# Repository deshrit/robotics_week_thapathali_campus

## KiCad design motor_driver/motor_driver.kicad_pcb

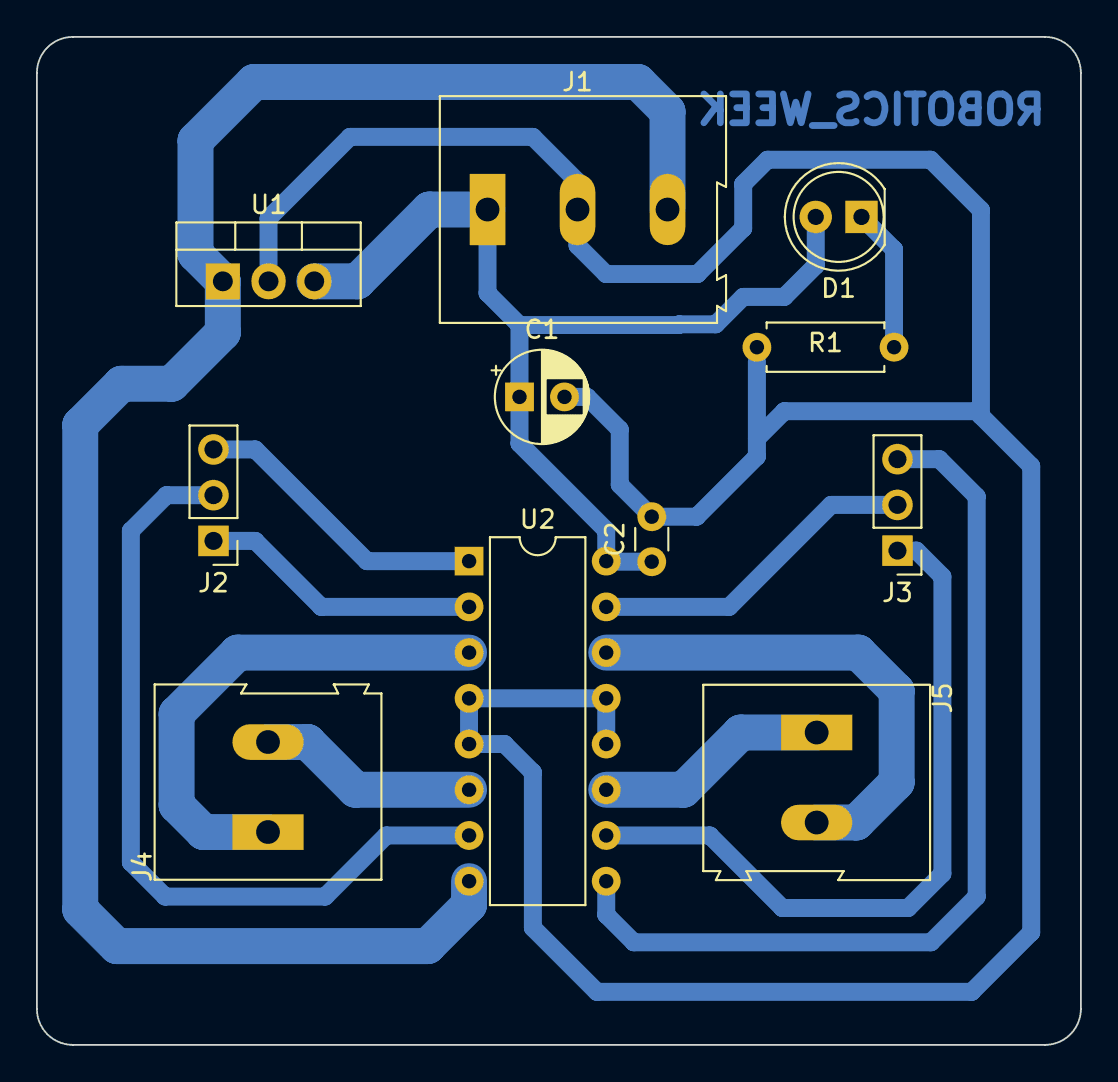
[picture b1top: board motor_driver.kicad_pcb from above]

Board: 2 copper layers, 58.0 x 56.0 mm, 11 parts (0 on the bottom side), 14 nets.

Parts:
C1: 100uf; CP_Radial_D5.0mm_P2.50mm
C2: 0.1uf; C_Disc_D3.0mm_W1.6mm_P2.50mm
D1: LED; LED_D5.0mm
J1: Conn_01x03_Female; TerminalBlock_Altech_AK300-3_P5.00mm
J2, J3: Conn_01x03_Male; PinHeader_1x03_P2.54mm_Vertical
J4, J5: Conn_01x02_Female; TerminalBlock_Altech_AK300-2_P5.00mm
R1: 220; R_Axial_DIN0207_L6.3mm_D2.5mm_P7.62mm_Horizontal
U1: L7805; TO-220-3_Vertical
U2: L293D; DIP-16_W7.62mm

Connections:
+5V: C1.1, C2.1, D1.2 (A), J1.1, U1.3 (OUT), U2.16 (VCC1)
+12V: J1.3, U1.1 (IN), U2.8 (VCC2)
GND: C1.2, C2.2, J1.2, R1.1, U1.2 (GND), U2.4 (GND), U2.5 (GND), U2.12 (GND), U2.13 (GND)
unnamed: D1.1 (K), R1.2
unnamed: J2.1, U2.2 (1A)
unnamed: J2.2, U2.7 (2A)
unnamed: J2.3, U2.1 (EN1,2)
unnamed: J3.1, U2.10 (3A)
unnamed: J3.2, U2.15 (4A)
unnamed: J3.3, U2.9 (EN3,4)
unnamed: J4.1, U2.3 (1Y)
unnamed: J4.2, U2.6 (2Y)
unnamed: J5.1, U2.11 (3Y)
unnamed: J5.2, U2.14 (4Y)
